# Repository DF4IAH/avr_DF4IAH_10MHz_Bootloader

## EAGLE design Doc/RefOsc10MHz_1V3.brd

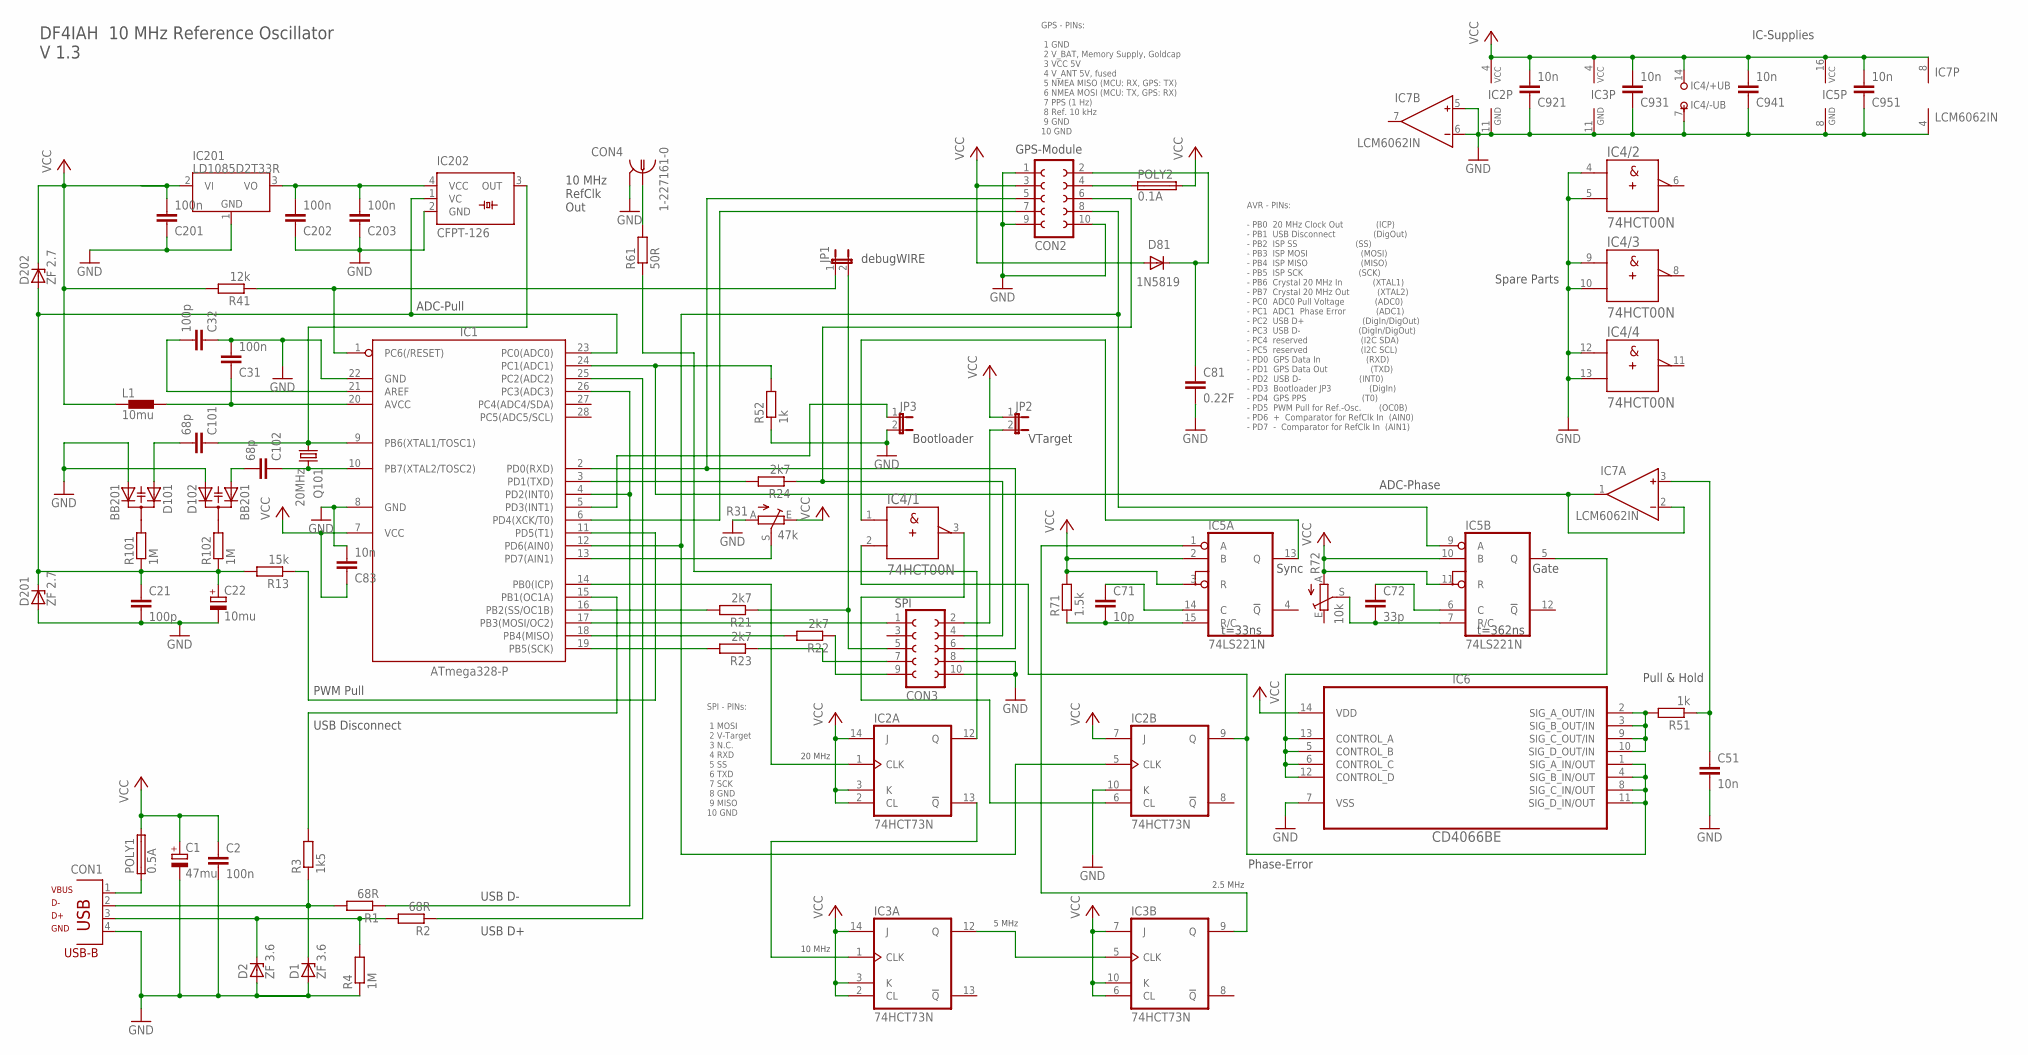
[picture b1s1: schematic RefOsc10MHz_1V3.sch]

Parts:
C1: 47mu; E2-4
C2, C31, C201, C202, C203: 100n; C5B3
C21, C32: 100p; C5B3
C22: 10mu; E2-4
C51, C83, C921, C931, C941, C951: 10n; C5B3
C71: 10p; C5B3
C72: 33p; C5B3
C81: 0.22F; C5B7.2
C101, C102: 68p; C5B3
CON1: PN61729
CON2, CON3: FE05-2
CON4: 1-227161-0; AMP_227161
D1, D2: ZF 3.6; DO41Z10
D81: 1N5819; DO41-10
D101, D102: BB201; SOT23
D201, D202: ZF 2.7; DO41Z10
IC1: ATmega328-P; DIL28-3
IC2, IC3: 74HCT73N; DIL14
IC4: 74HCT00N; DIL14
IC5: 74LS221N; DIL16
IC6: CD4066BE; DIP254P762X508-14
IC7: LCM6062IN; DIL08
IC201: LD10853.3; TO220V
IC202: CFPT-126; SM77H
JP1, JP2, JP3: JP1E; JP1
L1: 10mu; BL01RN1A
POLY1: 0.5A; TE5
POLY2: 0.1A; TE5
Q101: 20MHz; HC49U70
R1, R2: 68R; 0204/7
R3: 1k5; 0204/7
R4, R101, R102: 1M; 0204/7
R13: 15k; 0204/7
R21, R22, R23, R24: 2k7; 0204/7
R31: 47k; S64YW
R41: 12k; 0204/7
R51, R52: 1k; 0204/7
R61: 50R; 0204/7
R71: 1.5k; 0204/7
R72: 10k; S64YW

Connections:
GND: C1.-, C2.2, C21.2, C22.-, C31.2, C32.1, C51.2, C81.2, C83.2, C201.1, C202.1, C203.1, C921.1, C931.1, C941.1, C951.1, CON1.4, CON2.1, CON2.9, CON2.10, CON3.8, CON3.10, CON4.2, D1.A, D2.A, D101.2 (A2), D102.1 (A1), D201.A, IC1.8 (GND), IC1.22 (GND), IC2.10 (K), IC2.11 (GND), IC3.11 (GND), IC4.4 (A), IC4.5 (B), IC4.7 (-UB), IC4.9 (A), IC4.10 (B), IC4.12 (A), IC4.13 (B), IC5.8 (GND), IC6.7 (VSS), IC7.4 (V-), IC7.5 (IN+), IC7.6 (IN-), IC201.1 (GND), IC202.2 (GND), JP3.2, R4.1, R31.A, R52.1
N3V3: C202.2, C203.2, IC201.3 (VO), IC202.4 (VCC)
unnamed: C101.1, IC1.9 (PB6(XTAL1/TOSC1)), IC202.3 (OUT), Q101.1
unnamed: C102.1, IC1.10 (PB7(XTAL2/TOSC2)), Q101.2
unnamed: D102.3 (C), R102.2
unnamed: C101.2, D101.1 (A1)
unnamed: C21.1, C22.+, D201.C, D202.A, IC1.23 (PC0(ADC0)), IC202.1 (VC), R13.2, R101.1, R102.1
unnamed: CON1.2, D1.C, R1.2, R3.1
unnamed: CON1.3, D2.C, R2.2, R4.2
unnamed: IC1.4 (PD2(INT0)), IC1.26 (PC3(ADC3)), R1.1
unnamed: IC1.25 (PC2(ADC2)), R2.1
unnamed: IC1.16 (PB2(SS/OC1B)), R21.2
unnamed: CON3.1, IC1.17 (PB3(MOSI/OC2))
unnamed: IC1.19 (PB5(SCK)), R23.2
unnamed: C31.1, IC1.20 (AVCC), L1.2
unnamed: IC1.18 (PB4(MISO)), R22.2
unnamed: CON3.5, JP1.2, R21.1
unnamed: CON3.9, R22.1
unnamed: CON3.7, R23.1
unnamed: IC1.3 (PD1(TXD)), R24.2
unnamed: IC1.14 (PB0(ICP)), IC2.1 (CLK)
unnamed: CON2.5, CON3.6, IC1.2 (PD0(RXD))
unnamed: CON2.6, CON3.4, R24.1
unnamed: IC1.1 (PC6(/RESET)), JP1.1, R41.1
unnamed: CON3.2, JP2.2
unnamed: CON2.8, IC1.12 (PD6(AIN0)), IC2.5 (CLK), IC5.9 (A)
unnamed: IC1.13 (PD7(AIN1)), R31.S
unnamed: IC1.11 (PD5(T1)), R13.1
unnamed: C32.2, IC1.21 (AREF)
unnamed: IC1.5 (PD3(INT1)), JP3.1
unnamed: C102.2, D102.2 (A2)
unnamed: D101.3 (C), R101.2
unnamed: IC2.12 (Q), R61.1
unnamed: IC2.9 (Q), IC4.2 (B), IC6.1 (SIG_A_IN/OUT), IC6.4 (SIG_B_IN/OUT), IC6.8 (SIG_C_IN/OUT), IC6.11 (SIG_D_IN/OUT)
unnamed: IC6.2 (SIG_A_OUT/IN), IC6.3 (SIG_B_OUT/IN), IC6.9 (SIG_C_OUT/IN), IC6.10 (SIG_D_OUT/IN), R51.2
unnamed: C51.1, IC7.3 (IN+), R51.1
unnamed: IC2.6 (CL), IC4.3 (Y)
unnamed: IC5.5 (Q), IC6.5 (CONTROL_B), IC6.6 (CONTROL_C), IC6.12 (CONTROL_D), IC6.13 (CONTROL_A)
unnamed: IC1.24 (PC1(ADC1)), IC7.1 (OUT), IC7.2 (IN-), R52.2
unnamed: CON1.1, POLY1.1
unnamed: CON2.4, POLY2.1
unnamed: CON2.7, IC1.6 (PD4(XCK/T0))
unnamed: IC1.15 (PB1(OC1A)), R3.2
unnamed: CON4.1, R61.2
unnamed: IC4.1 (A), IC5.13 (Q)
unnamed: C72.2, IC5.7 (R/C), R72.S
unnamed: C72.1, IC5.6 (C)
unnamed: IC3.9 (Q), IC5.1 (A)
unnamed: C71.2, IC5.15 (R/C), R71.1
unnamed: C71.1, IC5.14 (C)
unnamed: IC2.13 (!Q), IC3.1 (CLK)
unnamed: IC3.5 (CLK), IC3.12 (Q)
unnamed: C81.1, CON2.2, D81.C
VCC: C1.+, C2.1, C83.1, C201.2, C921.2, C931.2, C941.2, C951.2, CON2.3, D81.A, D202.C, IC1.7 (VCC), IC2.2 (CL), IC2.3 (K), IC2.4 (VCC), IC2.7 (J), IC2.14 (J), IC3.2 (CL), IC3.3 (K), IC3.4 (VCC), IC3.6 (CL), IC3.7 (J), IC3.10 (K), IC3.14 (J), IC4.14 (+UB), IC5.2 (B), IC5.3 (R), IC5.10 (B), IC5.11 (R), IC5.16 (VCC), IC6.14 (VDD), IC7.8 (V+), IC201.2 (VI), JP2.1, L1.1, POLY1.2, POLY2.2, R31.E, R41.2, R71.2, R72.A

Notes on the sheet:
VTarget
debugWIRE
VBUS
GND
USB-B
AVR - PINs: - PB0 20 MHz Clock Out (ICP) - PB1 USB Disconnect (DigOut) - PB2 ISP SS (SS) - PB3 ISP MOSI (MOSI) - PB4 ISP MISO (MISO) - PB5 ISP SCK (SCK) - PB6 Crystal 20 MHz In (XTAL1) - PB7 Crystal 20 MHz Out (XTAL2) - PC0 ADC0 Pull Voltage (ADC0) - PC1 ADC1 Phase Error (ADC1) - PC2 USB D+ (DigIn/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
SPI
10 MHz RefClk Out
Bootloader
Phase-Error
Gate
GPS-Module
GPS - PINs: 1 GND 2 V_BAT, Memory Supply, Goldcap 3 VCC 5V 4 V_ANT 5V, fused 5 NMEA MISO (MCU: RX, GPS: TX) 6 NMEA MOSI (MCU: TX, GPS: RX) 7 PPS (1 Hz) 8 Ref. 10 kHz 9 GND 10 GND
Pull & Hold
ADC-Phase
PWM Pull
ADC-Pull
Sync
t=33ns
t=362ns
IC-Supplies
Spare Parts
20 MHz
10 MHz
5 MHz
2.5 MHz
DF4IAH 10 MHz Reference Oscillator V 1.3
USB Disconnect
USB D-
USB D+
SPI - PINs: 1 MOSI 2 V-Target 3 N.C. 4 RXD 5 SS 6 TXD 7 SCK 8 GND 9 MISO 10 GND

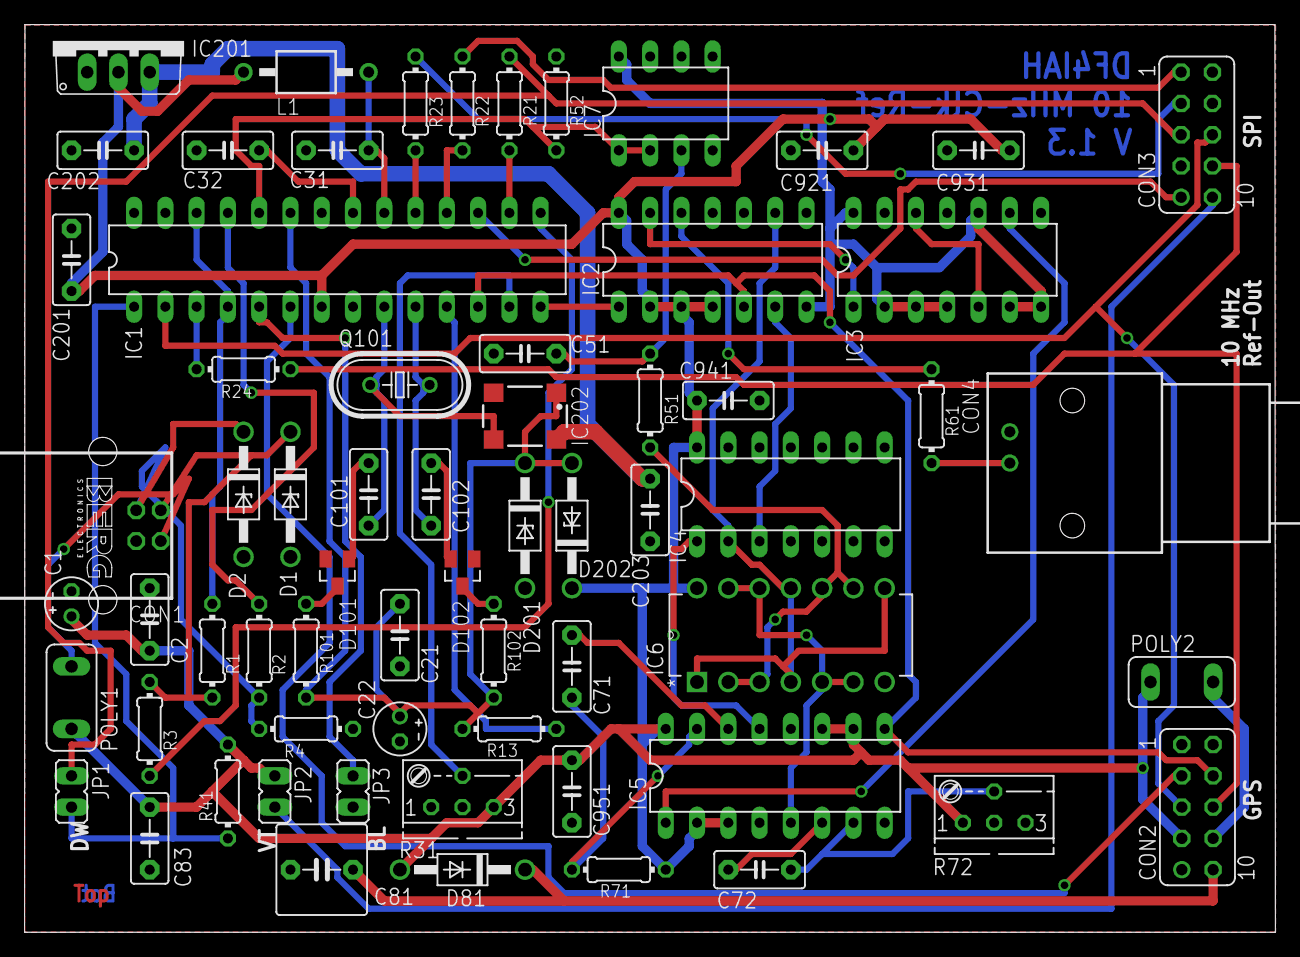
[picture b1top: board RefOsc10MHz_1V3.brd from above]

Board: 2 copper layers, 101.6 x 73.7 mm, 65 parts (0 on the bottom side), 54 nets.

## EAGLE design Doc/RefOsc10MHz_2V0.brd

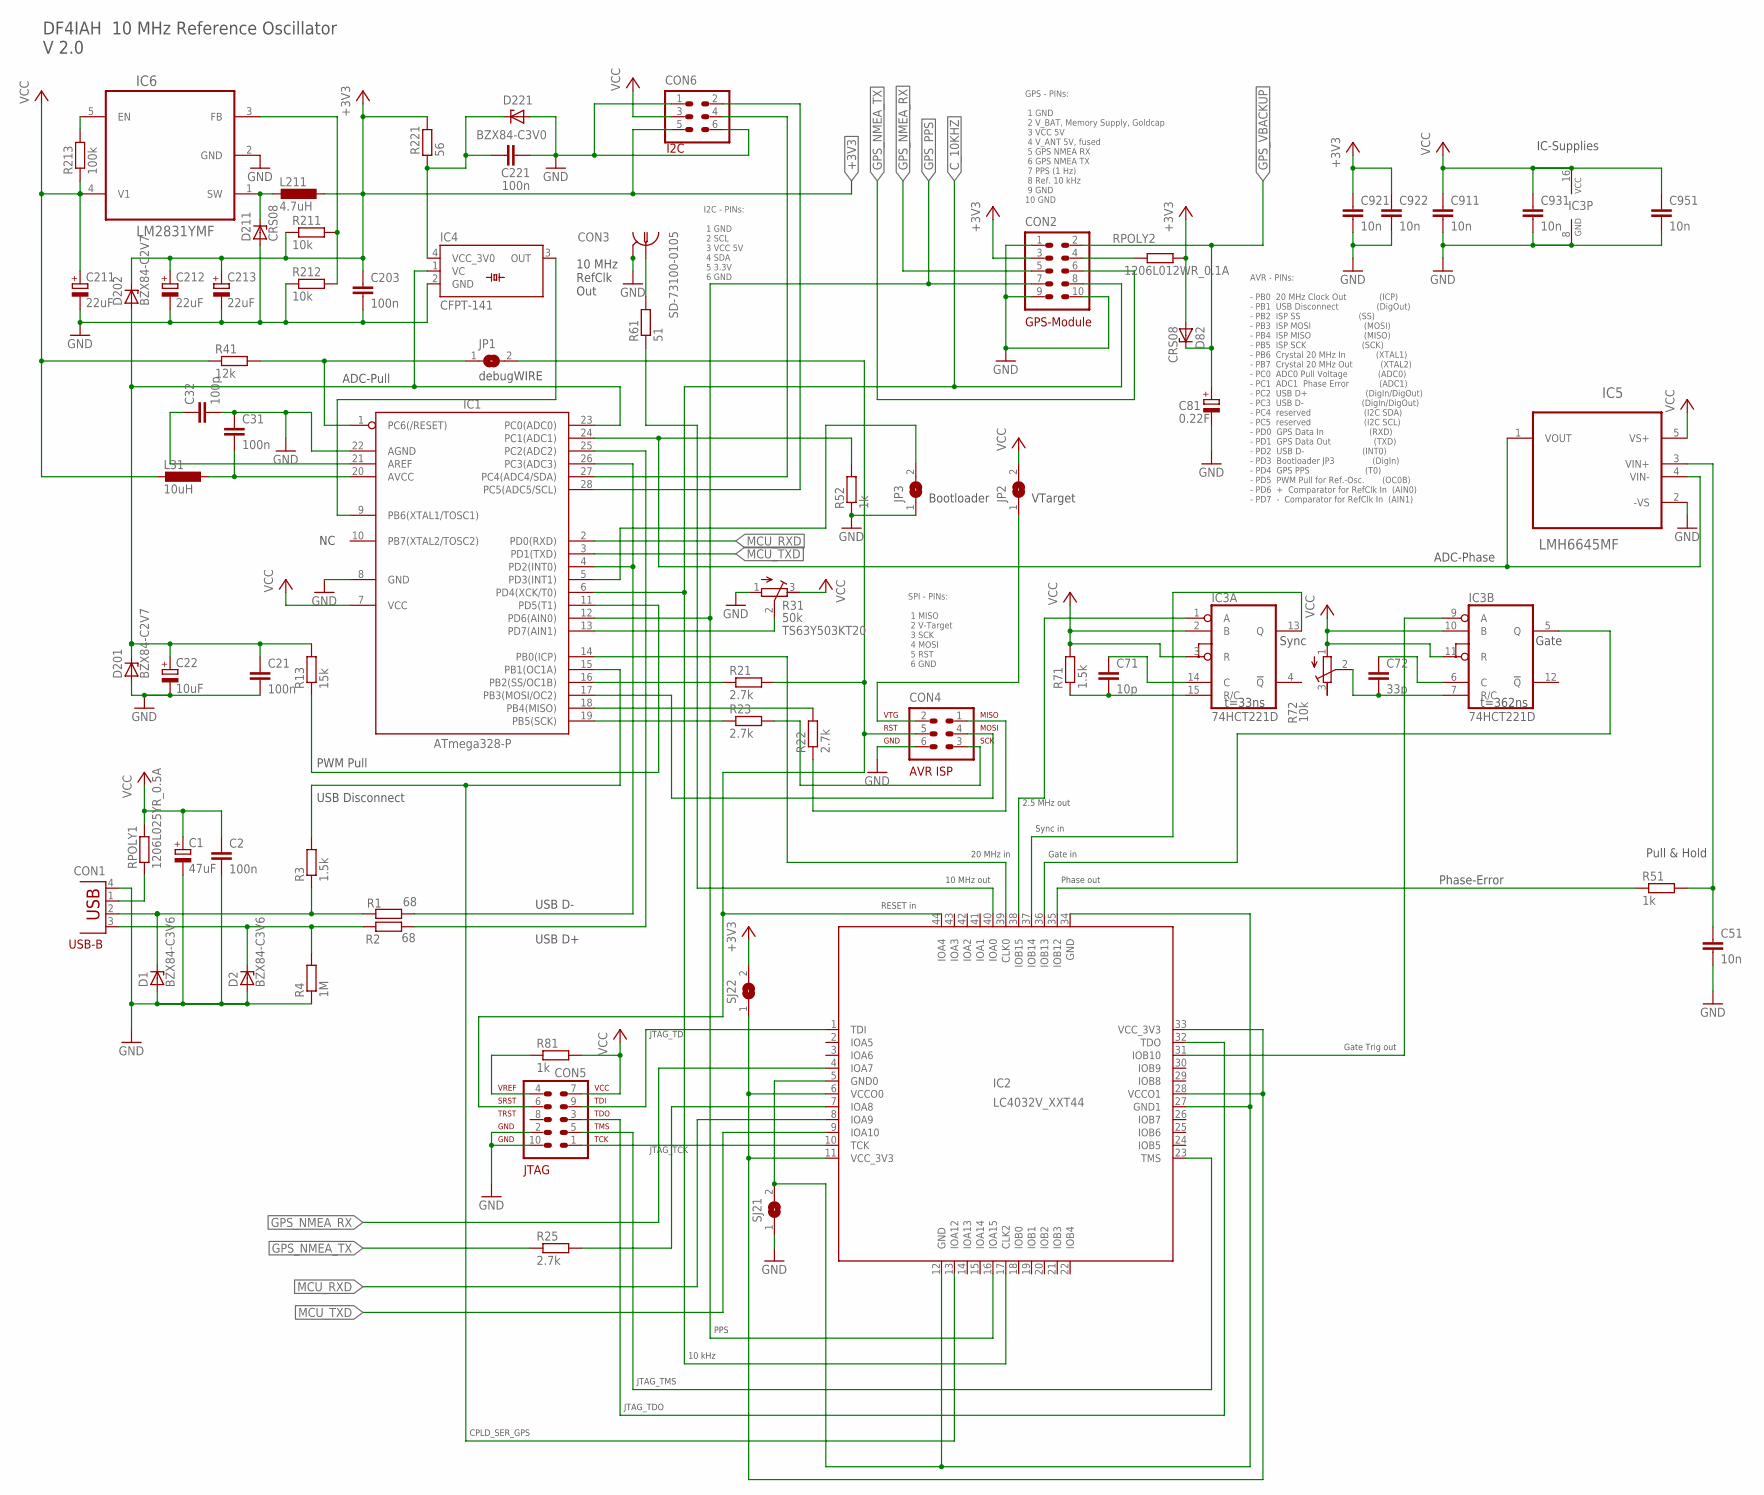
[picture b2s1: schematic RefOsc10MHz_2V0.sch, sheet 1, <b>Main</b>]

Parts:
C1: 47uF; PANASONIC_C
C2, C21, C31, C203, C221: 100n; C0805
C22: 10uF; PANASONIC_B
C32: 100p; C0805
C51, C911, C921, C922, C931, C951: 10n; C0805
C71: 10p; C0805
C72: 33p; C0805
C81: 0.22F; PANASONIC_C
C211, C212, C213: 22uF; A/3216-18W
CON1: TYCO-AMP_USBUSB-B_SMT; TYCO-AMP_USB-B_SMT
CON2: HEADER-2X5SMD; 2X5SMD
CON3: SD-73100-0105; MOLEX_BNC-JACK-50R_SD-73100-0105
CON4: AVR-ISP-6SMD; 2X3SMD
CON5: AVR-JTAG-10SMD; 2X5SMD
CON6: HEADER-2X3SMD; 2X03SMD
D1, D2: BZX84-C3V6; TO236
D82, D211: CRS08; SOT23
D201, D202: BZX84-C2V7; TO236
D221: BZX84-C3V0; TO236
IC1: ATmega328-P; DIL28-3
IC2: LC4032V_XXT44; TQFP44
IC3: 74HCT221D; SO16
IC4: CFPT-141
IC5: LMH6645MF; SOT95P280X145-5N
IC6: LM2831YMF; SOT95P280X145-5N
JP1, JP2, JP3: SJW
L31: 10uH; L1812
L211: 4.7uH; L5650M
R1, R2: 68; R0805
R3, R71: 1.5k; R0805
R4: 1M; R0805
R13: 15k; R0805
R21, R22, R23, R25: 2.7k; R0805
R31: 50k; RTRIMTS63Y
R41: 12k; R0805
R51, R52, R81: 1k; R0805
R61: 51; R0805
R72: 10k; RTRIMTS63Y
R211, R212: 10k; R0805
R213: 100k; R0805
R221: 56; R0805
RPOLY1: 1206L025YR_0.5A; M1206
RPOLY2: 1206L012WR_0.1A; M1206
SJ21, SJ22: SJ

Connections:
+3V0: C221.1, D221.C, IC4.4 (VCC_3V0), R221.2
+3V3: C203.1, C212.+, C213.+, C921.1, C922.1, CON2.3, CON6.5, D82.1 (A), D202.C, L211.1, R211.1, R221.1, RPOLY2.2, SJ22.2; also elsewhere on the board
ADC_PHASE: IC1.24 (PC1(ADC1)), IC5.1 (VOUT), IC5.4 (VIN-), R52.2
ADC_PHASE_PULLHOLD: C51.1, IC5.3 (VIN+), R51.2
AIN1: IC1.13 (PD7(AIN1)), R31.2 (S)
AREF: C32.1, IC1.21 (AREF)
AVCC: C31.2, IC1.20 (AVCC), L31.1
CPLD_GPS_NMEA_TX: IC2.7 (IOA8), R25.2
C_2MHZ5: IC2.38 (IOB15), IC3.1 (A)
C_10KHZ: CON2.8, IC1.6 (PD4(XCK/T0)), IC2.17 (CLK2)
C_10MHZ: IC2.40 (IOA0), R61.1
C_20MHZ: IC1.14 (PB0(ICP)), IC2.39 (CLK0)
EN: IC6.5 (EN), R213.2
FB: IC6.3 (FB), R211.2, R212.2
GATE: IC2.36 (IOB13), IC3.5 (Q)
GATE_TRIG: IC2.31 (IOB10), IC3.9 (A)
GND: C1.-, C2.2, C21.2, C22.-, C31.1, C32.2, C51.2, C81.-, C203.2, C211.-, C212.-, C213.-, C221.2, C911.2, C921.2, C922.2, C931.2, C951.2, CON1.4 (GND), CON2.1, CON2.9, CON2.10, CON3.2, CON3.3, CON4.6, CON5.2, CON5.10, CON6.1, CON6.6, D1.A, D2.A, D201.A, D211.1 (A), D221.A, IC1.8 (GND), IC1.22 (AGND), IC3.8 (GND), IC4.2 (GND), IC5.2 (-VS), IC6.2 (GND), JP3.1, R4.1, R31.1 (A), R52.1, R212.1, SJ21.1; also elsewhere on the board
GND_SJ1: IC2.5 (GND0), IC2.12 (GND), IC2.27 (GND1), IC2.34 (GND), SJ21.2
GPS_ANT_PWR: CON2.4, RPOLY2.1
GPS_NMEA_RX: CON2.5, IC2.4 (IOA7); also elsewhere on the board
GPS_NMEA_TX: CON2.6, R25.1; also elsewhere on the board
GPS_PPS: CON2.7, IC1.12 (PD6(AIN0)), IC2.16 (IOA15); also elsewhere on the board
GPS_VBACKUP: C81.+, CON2.2, D82.3 (C); also elsewhere on the board
INT1: IC1.5 (PD3(INT1)), JP3.2
ISP_MISO: CON4.1, R22.1
ISP_MOSI: CON4.4, IC1.17 (PB3(MOSI/OC2))
ISP_SCK: CON4.3, R23.2
ISP_VTARGET: CON4.2, JP2.1
JTAG_SRST: CON4.5, CON5.6, IC2.44 (IOA4), JP1.2, R21.2
JTAG_TCK: CON5.1, IC2.10 (TCK)
JTAG_TDI: CON5.9, IC2.1 (TDI)
JTAG_TDO: CON5.3, IC2.32 (TDO)
JTAG_TMS: CON5.5, IC2.23 (TMS)
JTAG_VREF: CON5.4, R81.1
MCU_RXD: IC1.2 (PD0(RXD)), IC2.8 (IOA9)
MCU_TXD: IC1.3 (PD1(TXD)), IC2.9 (IOA10)
MISO: IC1.18 (PB4(MISO)), R22.2
unnamed: CON6.2, IC1.28 (PC5(ADC5/SCL))
unnamed: CON6.4, IC1.27 (PC4(ADC4/SDA))
unnamed: CON3.1, R61.2
unnamed: C72.2, IC3.7 (R/C), R72.2 (S)
unnamed: C72.1, IC3.6 (C)
unnamed: C71.2, IC3.15 (R/C), R71.1
unnamed: C71.1, IC3.14 (C)
N_ADC_PULL: C21.1, C22.+, D201.C, D202.A, IC1.23 (PC0(ADC0)), IC4.1 (VC), R13.2
N_PWM_PULL: IC1.11 (PD5(T1)), R13.1
N_USB_DISC: IC1.15 (PB1(OC1A)), IC2.13 (IOA12), R3.2
N_USB_DMNS: IC1.4 (PD2(INT0)), IC1.26 (PC3(ADC3)), R1.2
N_USB_DPLS: IC1.25 (PC2(ADC2)), R2.2
PHASE_ERROR: IC2.35 (IOB12), R51.1
RESET: IC1.1 (PC6(/RESET)), JP1.1, R41.2
SCK: IC1.19 (PB5(SCK)), R23.1
SS: IC1.16 (PB2(SS/OC1B)), R21.1
SW: D211.3 (C), IC6.1 (SW), L211.2
SYNC: IC2.37 (IOB14), IC3.13 (Q)
TOSC1: IC1.9 (PB6(XTAL1/TOSC1)), IC4.3 (OUT)
USB_D_MIN: CON1.2 (D-), D1.C, R1.1, R3.1
USB_D_PLS: CON1.3 (D+), D2.C, R2.1, R4.2
USB_PWR: CON1.1 (VBUS), RPOLY1.1
VCC: C1.+, C2.1, C211.+, C911.1, C931.1, C951.1, CON5.7, CON6.3, IC1.7 (VCC), IC3.2 (B), IC3.3 (R), IC3.10 (B), IC3.11 (R), IC3.16 (VCC), IC5.5 (VS+), IC6.4 (V1), JP2.2, L31.2, R31.3 (E), R41.1, R71.2, R72.1 (A), R81.2, R213.1, RPOLY1.2
VCC_3V3_SJ2: IC2.6 (VCCO0), IC2.11 (VCC_3V3), IC2.28 (VCCO1), IC2.33 (VCC_3V3), SJ22.1

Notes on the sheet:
VTarget
debugWIRE
USB-B
AVR - PINs: - PB0 20 MHz Clock Out (ICP) - PB1 USB Disconnect (DigOut) - PB2 ISP SS (SS) - PB3 ISP MOSI (MOSI) - PB4 ISP MISO (MISO) - PB5 ISP SCK (SCK) - PB6 Crystal 20 MHz In (XTAL1) - PB7 Crystal 20 MHz Out (XTAL2) - PC0 ADC0 Pull Voltage (ADC0) - PC1 ADC1 Phase Error (ADC1) - PC2 USB D+ (DigIn/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
10 MHz RefClk Out
Bootloader
Phase-Error
Gate
GPS-Module
GPS - PINs: 1 GND 2 V_BAT, Memory Supply, Goldcap 3 VCC 5V 4 V_ANT 5V, fused 5 GPS NMEA RX 6 GPS NMEA TX 7 PPS (1 Hz) 8 Ref. 10 kHz 9 GND 10 GND
Pull & Hold
ADC-Phase
PWM Pull
ADC-Pull
Sync
t=33ns
t=362ns
IC-Supplies
20 MHz in
10 MHz out
2.5 MHz out
DF4IAH 10 MHz Reference Oscillator V 2.0
USB Disconnect
USB D-
USB D+
SPI - PINs: 1 MISO 2 V-Target 3 SCK 4 MOSI 5 RST 6 GND
10 kHz
Sync in
Gate in
Phase out
PPS
RESET in
Gate Trig out
JTAG_TMS
JTAG_TDO
JTAG_TCK
JTAG_TDI
CPLD_SER_GPS
I2C - PINs: 1 GND 2 SCL 3 VCC 5V 4 SDA 5 3.3V 6 GND
I2C

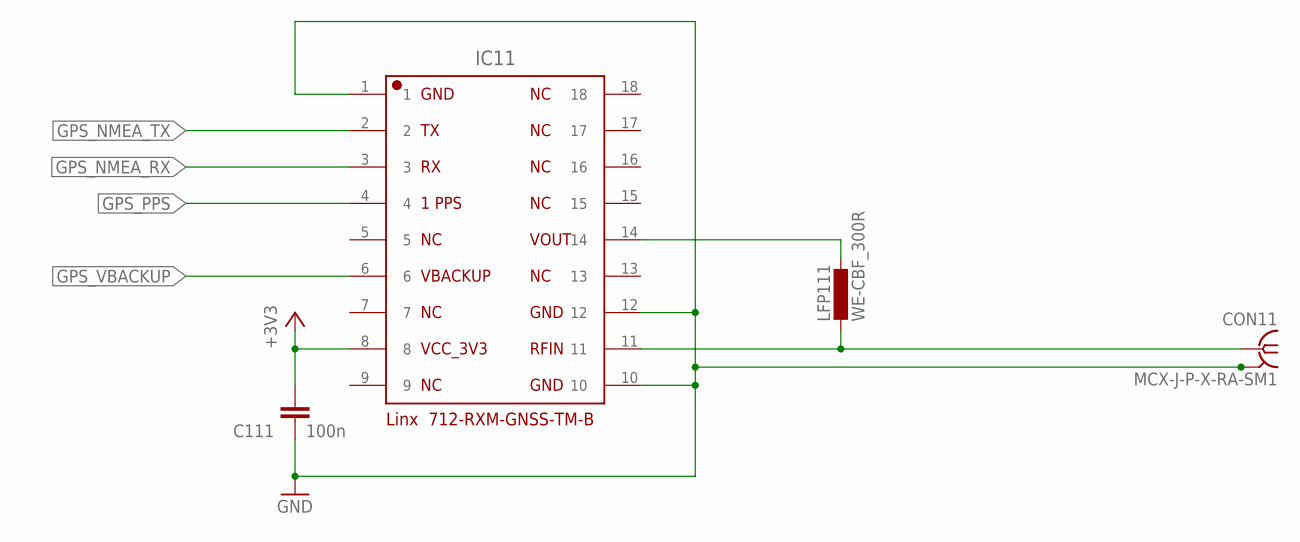
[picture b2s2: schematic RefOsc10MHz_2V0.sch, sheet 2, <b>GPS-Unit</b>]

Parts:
C111: 100n; C0805
CON11: MCX-J-P-X-RA-SM1
IC11: 712-RXM-GNSS-TM-B
LFP111: WE-CBF_300R; L3216C

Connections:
14: IC11.14, LFP111.1
+3V3: C111.1, IC11.8; also elsewhere on the board
GND: C111.2, CON11.2, CON11.3, CON11.4, CON11.5, IC11.1, IC11.10, IC11.12; also elsewhere on the board
GPS_HF: CON11.1, IC11.11, LFP111.2
GPS_NMEA_RX: IC11.3; also elsewhere on the board
GPS_NMEA_TX: IC11.2; also elsewhere on the board
GPS_PPS: IC11.4; also elsewhere on the board
GPS_VBACKUP: IC11.6; also elsewhere on the board

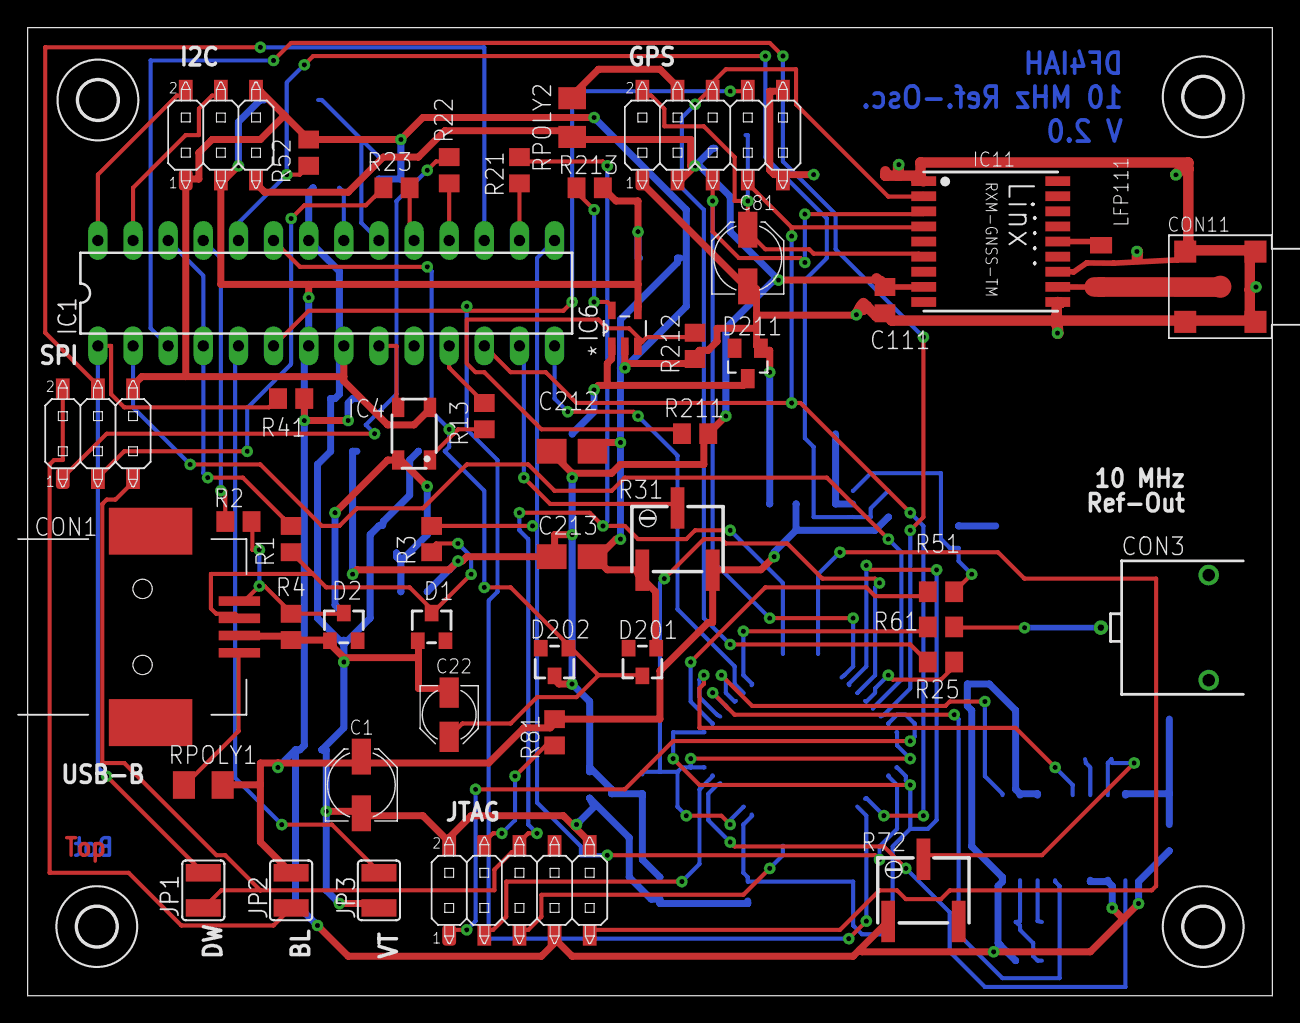
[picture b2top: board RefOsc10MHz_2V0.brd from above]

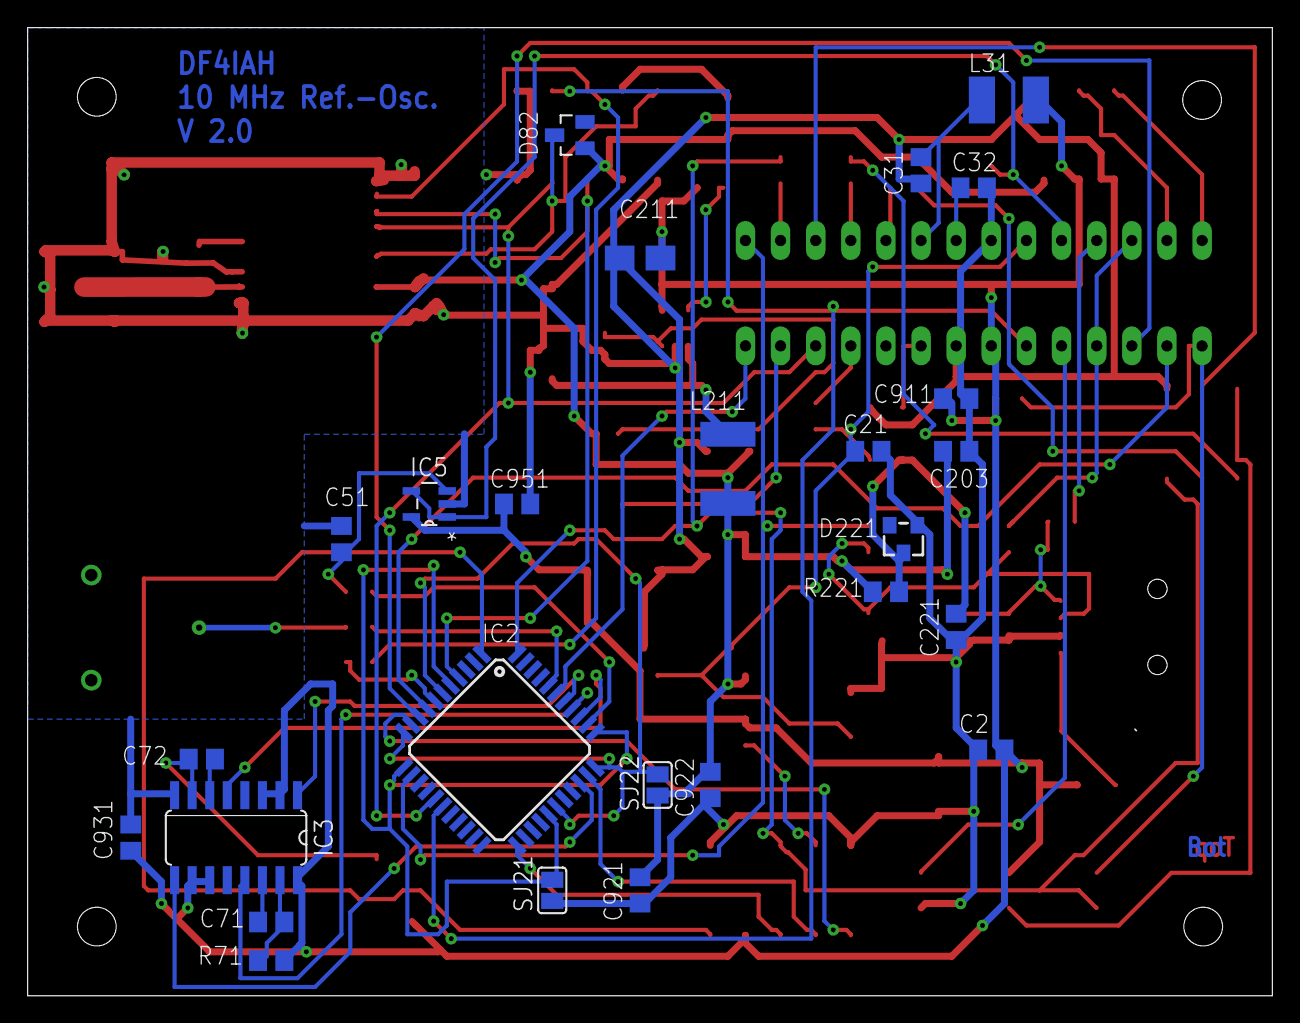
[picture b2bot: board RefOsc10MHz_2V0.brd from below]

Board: 2 copper layers, 90.0 x 70.0 mm, 77 parts (26 on the bottom side), 63 nets.

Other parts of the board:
U$1, U$2, U$3, U$4: 2,8

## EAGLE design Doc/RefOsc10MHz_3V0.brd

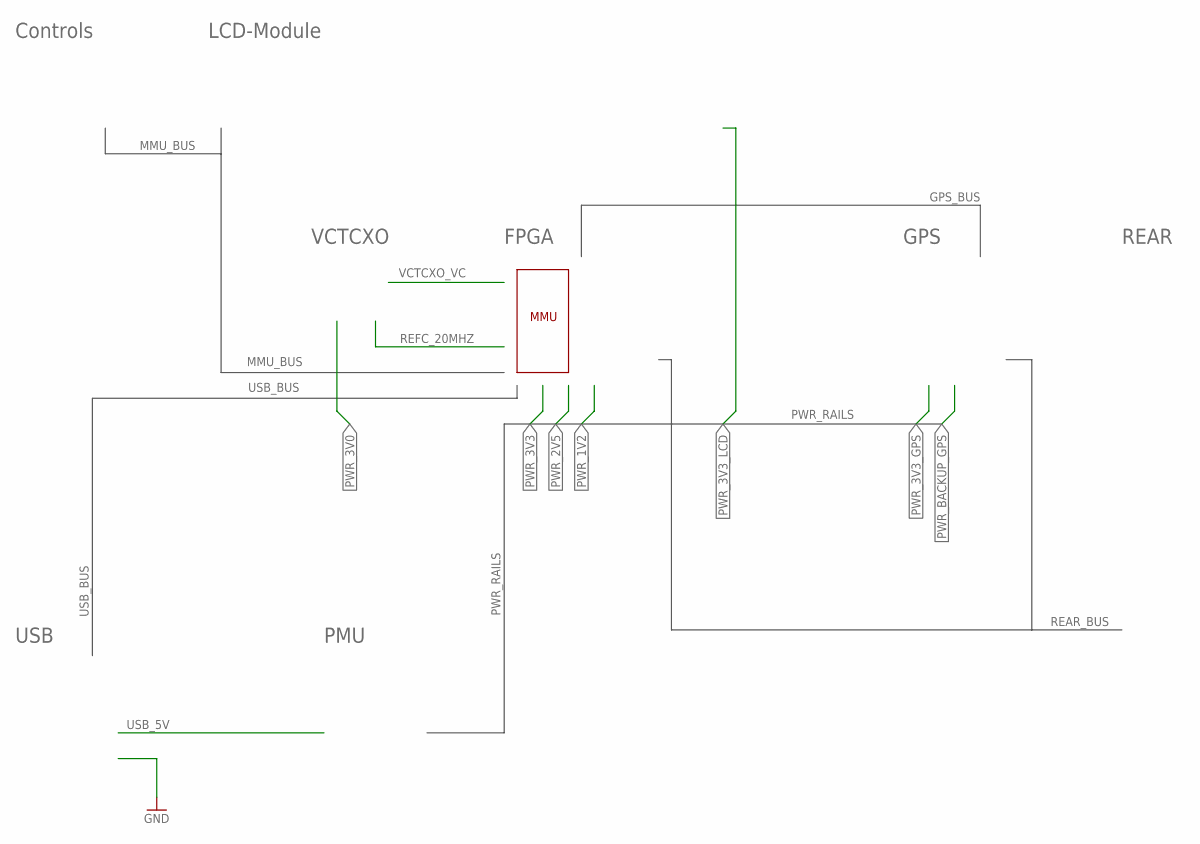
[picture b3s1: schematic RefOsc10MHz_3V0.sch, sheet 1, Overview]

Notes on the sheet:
VCTCXO
FPGA
GPS
REAR
LCD-Module
Controls
USB
PMU
MMU

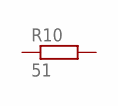
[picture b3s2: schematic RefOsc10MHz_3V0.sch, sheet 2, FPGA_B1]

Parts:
R10: 51; R0805

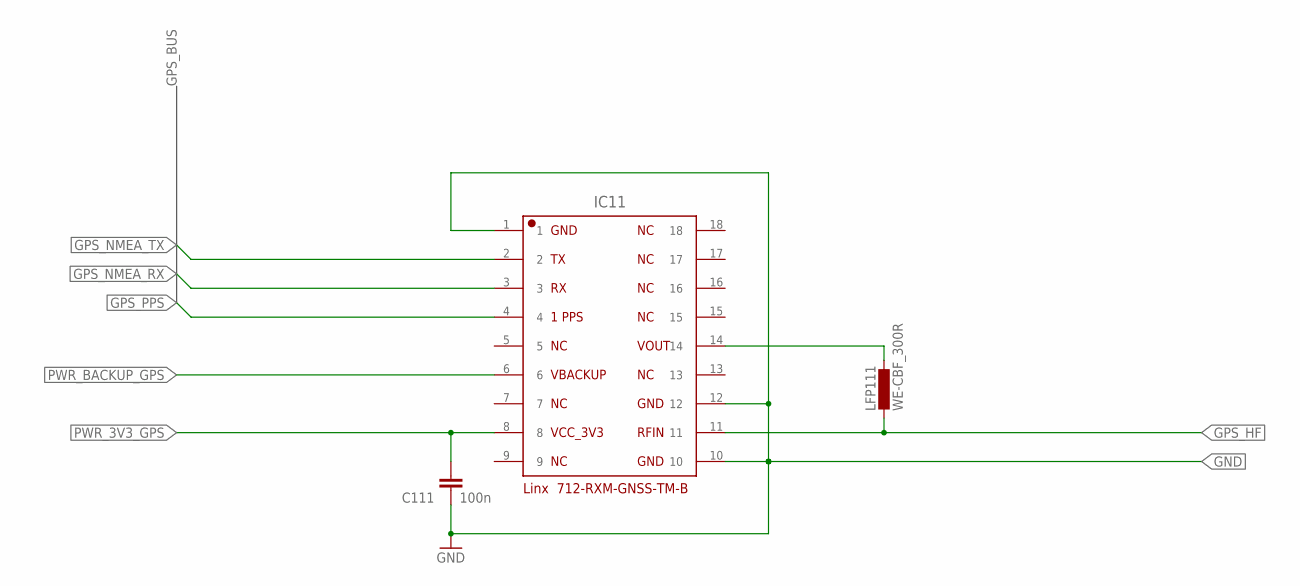
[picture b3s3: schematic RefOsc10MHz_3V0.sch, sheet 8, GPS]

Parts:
C111: 100n; C0805
IC11: 712-RXM-GNSS-TM-B
LFP111: WE-CBF_300R; L3216C

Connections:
14: IC11.14, LFP111.1
GND: C111.2, IC11.1, IC11.10, IC11.12; also elsewhere on the board
GPS_HF: IC11.11, LFP111.2; also elsewhere on the board
GPS_NMEA_RX: IC11.3
GPS_NMEA_TX: IC11.2; also elsewhere on the board
GPS_PPS: IC11.4
PWR_3V3_GPS: C111.1, IC11.8
PWR_BACKUP_GPS: IC11.6; also elsewhere on the board

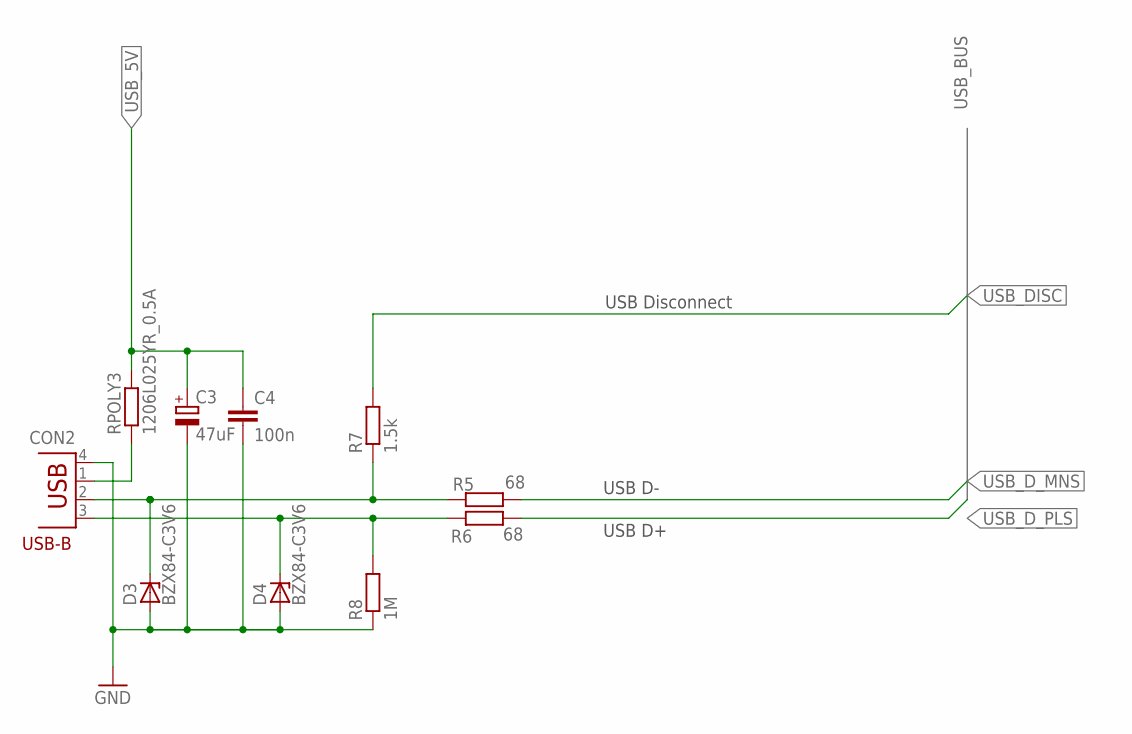
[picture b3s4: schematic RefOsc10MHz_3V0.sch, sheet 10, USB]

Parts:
C3: 47uF; PANASONIC_C
C4: 100n; C0805
CON2: TYCO-AMP_USBUSB-B_SMT; TYCO-AMP_USB-B_SMT
D3, D4: BZX84-C3V6; TO236
R5, R6: 68; R0805
R7: 1.5k; R0805
R8: 1M; R0805
RPOLY3: 1206L025YR_0.5A; M1206

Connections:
GND: C3.-, C4.2, CON2.4 (GND), D3.A, D4.A, R8.1; also elsewhere on the board
USB_5V: C3.+, C4.1, RPOLY3.2
USB_DISC: R7.2
USB_D_MIN1: CON2.2 (D-), D3.C, R5.1, R7.1
USB_D_MNS: R5.2
USB_D_PLS: R6.2
USB_D_PLS1: CON2.3 (D+), D4.C, R6.1, R8.2
USB_PWR1: CON2.1 (VBUS), RPOLY3.1

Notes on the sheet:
USB-B
USB Disconnect
USB D-
USB D+

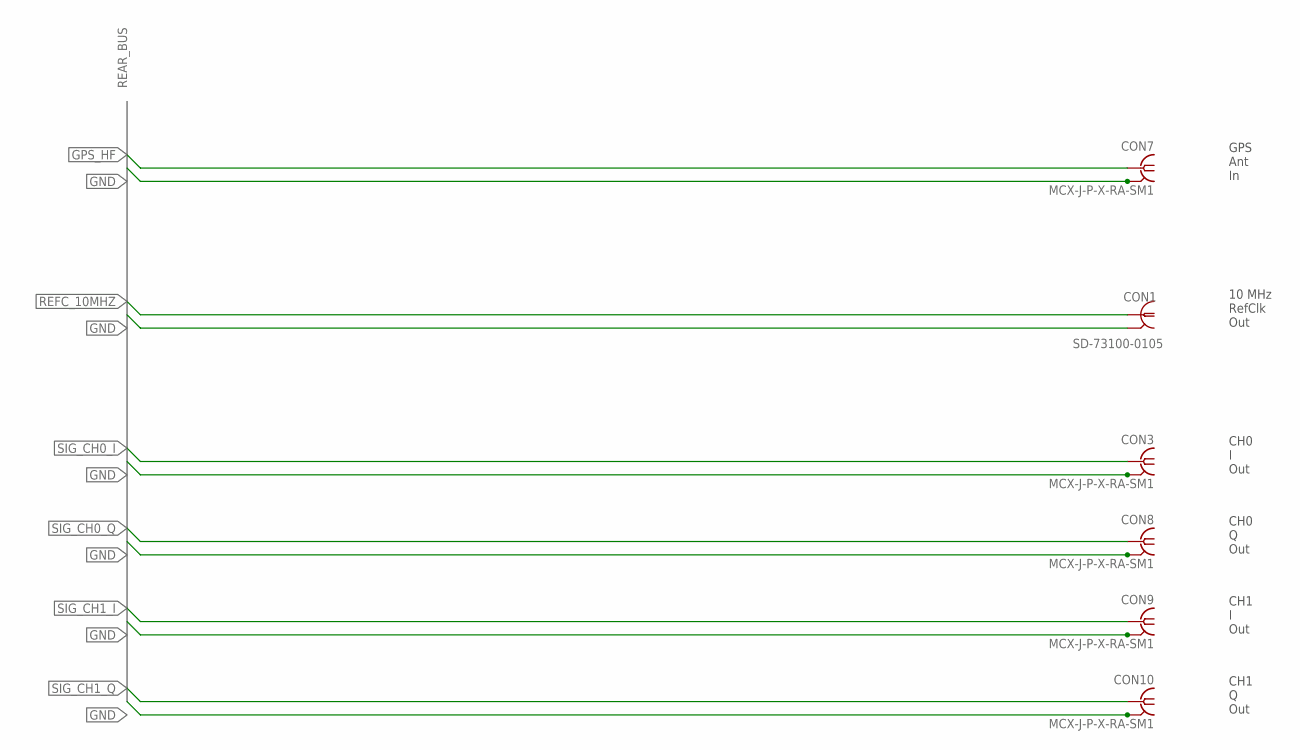
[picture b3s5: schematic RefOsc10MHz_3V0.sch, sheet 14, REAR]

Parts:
CON1: SD-73100-0105; MOLEX_BNC-JACK-50R_SD-73100-0105
CON3, CON7, CON8, CON9, CON10: MCX-J-P-X-RA-SM1

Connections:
GND: CON1.2, CON1.3, CON3.2, CON3.3, CON3.4, CON3.5, CON7.2, CON7.3, CON7.4, CON7.5, CON8.2, CON8.3, CON8.4, CON8.5, CON9.2, CON9.3, CON9.4, CON9.5, CON10.2, CON10.3, CON10.4, CON10.5; also elsewhere on the board
GPS_HF: CON7.1; also elsewhere on the board
REFC_10MHZ: CON1.1
SIG_CH0_I: CON3.1
SIG_CH0_Q: CON8.1
SIG_CH1_I: CON9.1
SIG_CH1_Q: CON10.1

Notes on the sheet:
10 MHz RefClk Out
GPS Ant In
CH0 I Out
CH0 Q Out
CH1 I Out
CH1 Q Out
